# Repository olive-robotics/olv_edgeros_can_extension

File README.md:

# Olive Robotics EdgeROS SOM01-X CAN Carrier Board

## Overview

This repository contains the KiCad project files for a carrier board designed to interface with the Olive Robotics EdgeROS SOM01-X. The carrier board connects via the 2x18 pin connector on the EdgeROS and provides a CAN interface.

## Features

- 2x18 pin connector for interfacing with EdgeROS SOM01-X
- CAN interface
- Designed using KiCad

## Prerequisites

- KiCad 7.0.1 or higher
- Basic understanding of PCB design and electronics

## Getting Started

1. **Clone the Repository**: Clone or download this repository to your local machine.
2. **Open the Project**: Navigate to the directory where you cloned the repository and open the KiCad project file.
3. **Review the Schematic**: Open the schematic editor to review the connections.
4. **Inspect the Layout**: Open the PCB layout editor to review or modify the board layout.
5. **Generate Gerber Files**: Once you are satisfied with the design, generate the Gerber files for manufacturing.

## Usage

1. **Assembly**: Solder the 2x18 pin connector and the USB 2.0 interface components onto the carrier board.
2. **Connection**: Connect the carrier board to the EdgeROS SOM01-X using the 2x18 pin connector.
3. **Testing**: Power up the EdgeROS and connect a CAN device to test the interface.

## Contributing

If you find any issues or have suggestions for improvements, feel free to open an issue or submit a pull request.

## License

This project is open-source and available under the MIT License. See the `LICENSE.md` file for more information.

## Contact

For any questions or inquiries, please contact Olive Robotics at [contact@olive-robotics.com](mailto:contact@olive-robotics.com).

---

Happy building! 🤖

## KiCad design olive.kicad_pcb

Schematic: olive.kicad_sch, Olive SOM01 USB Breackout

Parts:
C1, C3, C4: 100nF; C_0402_1005Metric
C2: 220uF 6.3v Case(mm)3228; CP_EIA-3528-21_Kemet-B
D1, D2: LED; LED_0603_1608Metric
H1, H2, H3, H4: MountingHole_Pad; MountingHole_2.2mm_M2_ISO7380_Pad
J2: Conn_02x18_Odd_Even; PinHeader_2x18_P1.27mm_Vertical_SMD
J3: Conn_01x04_Male; Molex_PicoBlade_53261-0471_1x04-1MP_P1.25mm_Horizontal
R1: 10K; R_0402_1005Metric
R2: 120R (DNP); R_0402_1005Metric
R3: 1K; R_0402_1005Metric
U1: TCAN1051HGV-Q1; Texas_DRB0008A-X

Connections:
+3V3: C4.1, J2.4, U1.5 (SHDN)
+5V: C1.1, C2.1, C3.1, D1.2 (A), J2.2, J3.4, U1.3 (VCC)
/CAN_RX: J2.17, U1.4 (RXD)
/CAN_ST: J2.3, U1.8 (S)
/CAN_TX: J2.19, U1.1 (TXD)
/I2C1_SCL: J2.15
/I2C1_SDA: J2.13
/I2C6_SCL: J2.16
/I2C6_SDA: J2.14
/OSD_ADC_0: J2.36
/OSD_ADC_1: J2.34
/OSD_ADC_2: J2.32
/OSD_ADC_3: J2.30
/OSD_ADC_4: J2.28
/OSD_ADC_5: J2.26
/OSD_ADC_6: J2.24
/OSD_ADC_7: J2.22
/OSD_PWM_0: D2.2 (A), J2.21
/OSD_PWM_1: J2.23
/OSD_PWM_2: J2.25
/OSD_PWM_3: J2.27
/OSD_PWM_4: J2.29
/OSD_PWM_5: J2.31
/OSD_PWM_6: J2.33
/OSD_PWM_7: J2.35
/SPI-CLK: J2.7
/SPI-MISO: J2.9
/SPI-MOSI: J2.11
/SPI-NSS: J2.5
/TTL_RXD: J2.18
/TTL_TXD: J2.20
/USB_OSD1_D_N: J2.8
/USB_OSD1_D_P: J2.6
/USB_OSD_D_N: J2.12
/USB_OSD_D_P: J2.10
GND: C1.2, C2.2, C3.2, C4.2, H1.1, H2.1, H3.1, H4.1, J2.1, J3.1, J3.MP, R1.1, R3.1, U1.2 (GND)
unnamed: D1.1 (K), R1.2
unnamed: D2.1 (K), R3.2
unnamed: J3.2, R2.1, U1.6 (CANL)
unnamed: J3.3, R2.2, U1.7 (CANH)

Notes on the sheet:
PWR LEDs
Note: 3.3v Max 1800mA +5.0v Max 2000mA
Olive Robotics SOM01-X EdgeROS SOM Platform (c) Copyright, Olive Robotics GmbH, 2021 - Dec. All Rights Reserved.
CAN TX-RX LED
Screw Pads
Note: To control the PWM signals, use the following files in the Oive Robotics OLIX RT Linux Kernel. /sys/class/pwm/pwmchip4/pwm3/duty_cycle /sys/class/pwm/pwmchip4/pwm2/duty_cycle /sys/class/pwm/pwmchip4/pwm1/duty_cycle /sys/class/pwm/pwmchip4/pwm0/duty_cycle /sys/class/pwm/pwmchip0/pwm3/duty_cycl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
Note: To read the adc data, use the following files in the Oive Robotics OLIX RT Linux Kernel. /sys/bus/iio/devices/iio:device0/in_voltage1_raw /sys/bus/iio/devices/iio:device0/in_voltage2_raw /sys/bus/iio/devices/iio:device0/in_voltage4_raw /sys/bus/iio/devices/iio:device0/in_voltage5_raw /sys/bus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
Note: DO Not USE! USB_OSD_D_N & USB_OSD_D_P

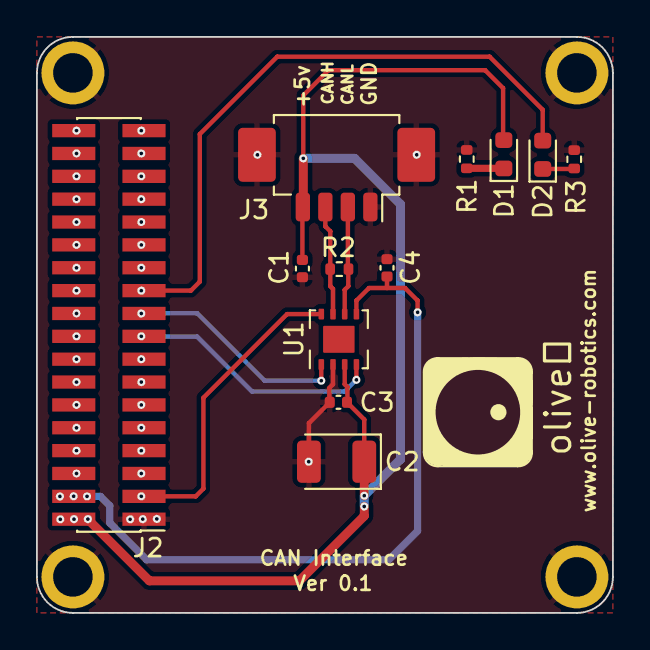
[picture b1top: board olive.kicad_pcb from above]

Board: 2 copper layers, 32.0 x 32.0 mm, 16 parts (0 on the bottom side), 11 nets.

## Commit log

2023-11-01 The Can driver
2024-01-27 Update README.md
    Added the 3D image of the board to the README.md
